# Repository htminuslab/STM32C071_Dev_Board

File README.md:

# STM32C071G8 Development Board
This repository contains a tiny STM32C071G8U6N development board developed in [KiCAD8](https://www.kicad.org/). The board took just 1 day to develop and another few hours sorting out some [JLCPCB](https://jlcpcb.com/) issues (wrong/shifted part alignments, selecting parts from [LCSC](https://www.lcsc.com/) etc). 

**Note this board has not yet been manufacturered (JLCPCB gave a quote for £47{UK} for 5 Boards).**

The boards is nothing more but a USB-C connector, STM32C071 and a 3.3v power regulator. Schematics/PBC/Manufacturing data is located in the KiCAD directory.

## License

See the LICENSE file for details.

## Trademarks

STM32 is a registered trademark of STMicroelectronics International N.V.

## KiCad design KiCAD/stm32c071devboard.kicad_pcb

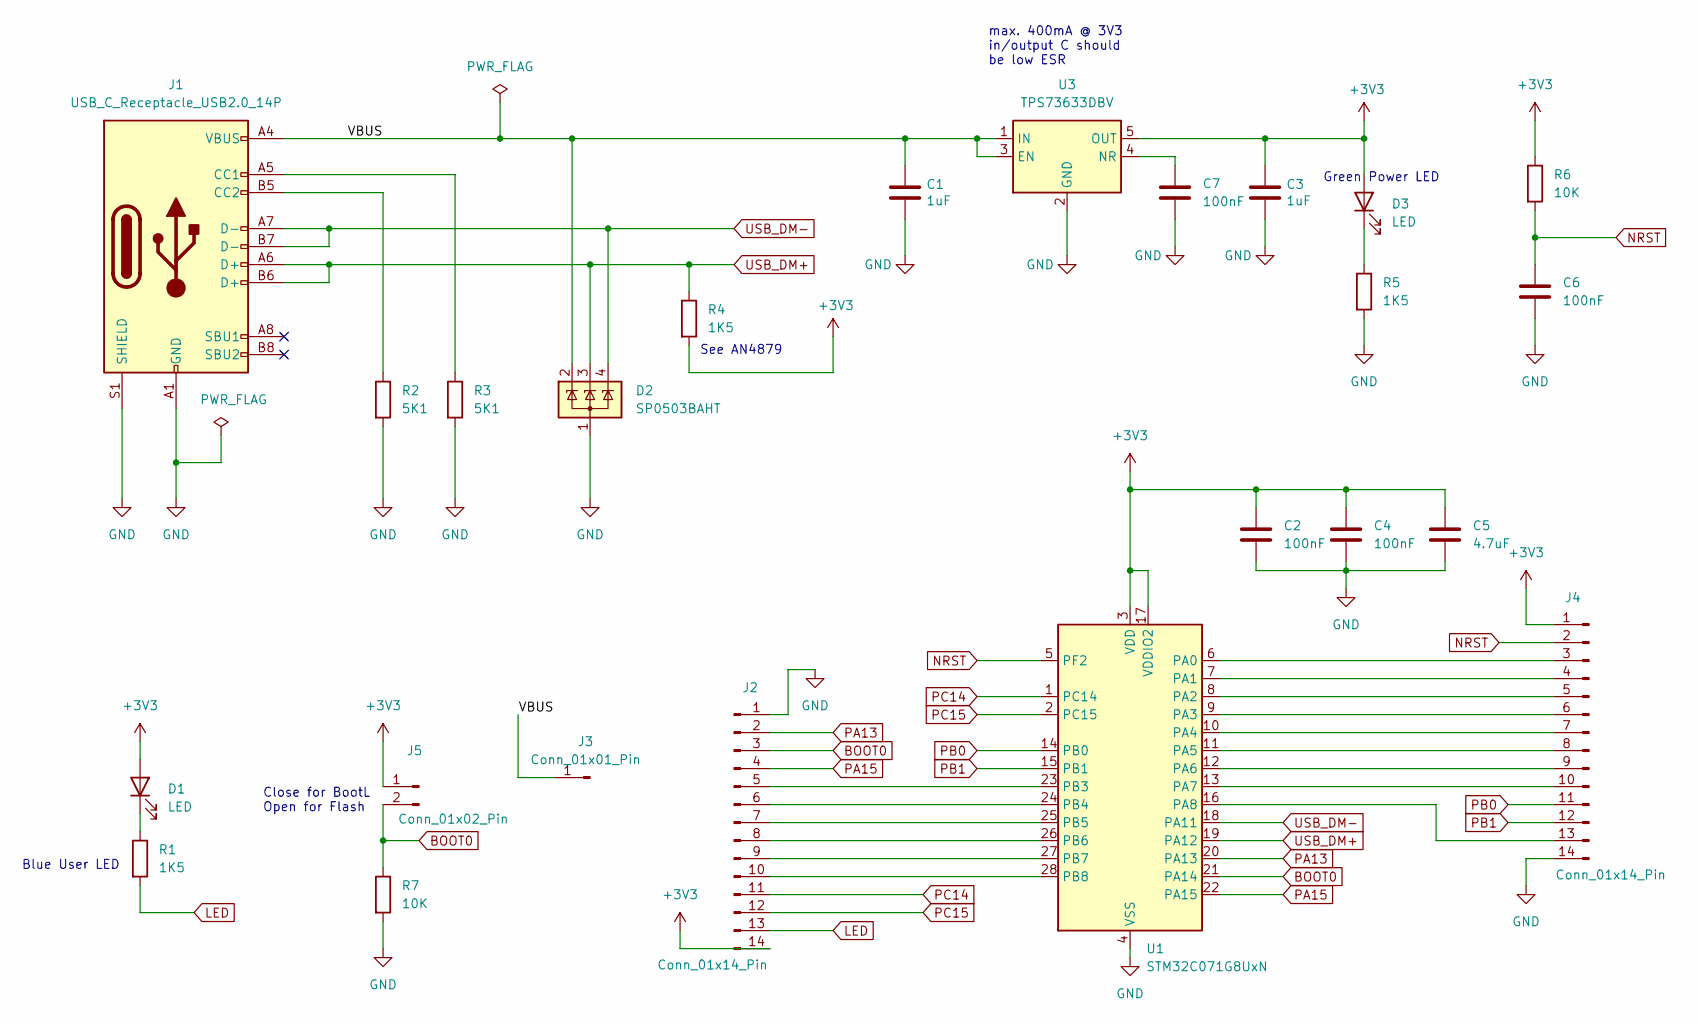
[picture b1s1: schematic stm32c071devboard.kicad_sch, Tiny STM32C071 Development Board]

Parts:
C1, C3: 1uF; C_0805_2012Metric
C2, C4, C6, C7: 100nF; C_0402_1005Metric
C5: 4.7uF; C_0805_2012Metric
D1, D3: LED; LED_0603_1608Metric
D2: SP0503BAHT; SOT-143
J1: USB_C_Receptacle_USB2.0_14P; USB_C_Receptacle_G-Switch_GT-USB-7010ASV_mod
J2, J4: Conn_01x14_Pin; PinHeader_1x14_P2.54mm_Vertical
J3: Conn_01x01_Pin; PinHeader_1x01_P1.00mm_Vertical
J5: Conn_01x02_Pin; PinHeader_1x02_P1.00mm_Vertical
R1, R4, R5: 1K5; R_0402_1005Metric
R2, R3: 5K1; R_0402_1005Metric
R6, R7: 10K; R_0402_1005Metric
U1: STM32C071G8UxN; QFN-28_4x4mm_P0.5mm
U3: TPS73633DBV; SOT-23-5

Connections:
+3V3: C2.1, C3.1, C4.1, C5.1, D1.2 (A), D3.2 (A), J2.14, J4.1, J5.1, R4.2, R6.1, U1.3 (VDD), U1.17 (VDDIO2), U3.5 (OUT)
/VBUS: C1.1, D2.2 (K), J1.A4 (VBUS), J1.A9 (VBUS), J1.B4 (VBUS), J1.B9 (VBUS), J3.1, U3.1 (IN), U3.3 (EN)
BOOT0: J2.3, J5.2, R7.1, U1.21 (PA14)
GND: C1.2, C2.2, C3.2, C4.2, C5.2, C6.2, C7.2, D2.1 (A), J1.A1 (GND), J1.A12 (GND), J1.B1 (GND), J1.B12 (GND), J1.S1 (SHIELD), J2.1, J4.14, R2.2, R3.2, R5.2, R7.2, U1.4 (VSS), U3.2 (GND)
LED: J2.13, R1.2
NRST: C6.1, J4.2, R6.2, U1.5 (PF2)
unnamed: D1.1 (K), R1.1
unnamed: D3.1 (K), R5.1
unnamed: J1.A5 (CC1), R3.1
unnamed: J1.B5 (CC2), R2.1
unnamed: J2.5, U1.23 (PB3)
unnamed: J2.6, U1.24 (PB4)
unnamed: J2.7, U1.25 (PB5)
unnamed: J2.8, U1.26 (PB6)
unnamed: J2.9, U1.27 (PB7)
unnamed: J2.10, U1.28 (PB8)
unnamed: J4.3, U1.6 (PA0)
unnamed: J4.4, U1.7 (PA1)
unnamed: J4.5, U1.8 (PA2)
unnamed: J4.6, U1.9 (PA3)
unnamed: J4.7, U1.10 (PA4)
unnamed: J4.8, U1.11 (PA5)
unnamed: J4.9, U1.12 (PA6)
unnamed: J4.10, U1.13 (PA7)
unnamed: J4.13, U1.16 (PA8)
unnamed: C7.1, U3.4 (NR)
PA13: J2.2, U1.20 (PA13)
PA15: J2.4, U1.22 (PA15)
PB0: J4.11, U1.14 (PB0)
PB1: J4.12, U1.15 (PB1)
PC14: J2.11, U1.1 (PC14)
PC15: J2.12, U1.2 (PC15)
USB_DM+: D2.3 (K), J1.A6 (D+), J1.B6 (D+), R4.1, U1.19 (PA12)
USB_DM-: D2.4 (K), J1.A7 (D-), J1.B7 (D-), U1.18 (PA11)

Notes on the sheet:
Close for BootL Open for Flash
max. 400mA @ 3V3 in/output C should be low ESR
Blue User LED
See AN4879
Green Power LED

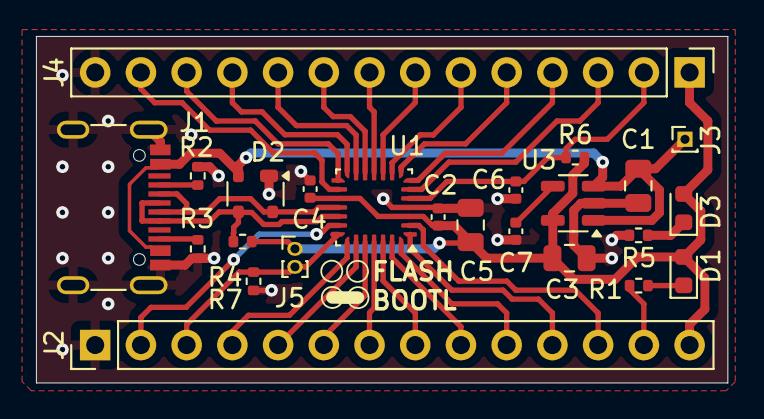
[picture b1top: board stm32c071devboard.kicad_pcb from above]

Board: 2 copper layers, 38.4 x 19.2 mm, 24 parts (0 on the bottom side), 34 nets.

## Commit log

2025-02-10 Development Board
    Simple STM32C071G8U6N development board in KiCad8
2025-02-11 Fixed 2 pins
2025-02-15 Minor mods
    Top level ground plane and a few stitching vias
